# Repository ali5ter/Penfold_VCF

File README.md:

> **⚠️ Archived 2025-08-25. No longer maintained.**

# Penfold_VCF
[KiCad](https://www.kicad.org/) project for the circuit and PCB of R.A. Penfolds VCF design which I adapted as a Eurorack powered module.
The original circuit is taken from [the book, "Electronic Synthesiser Construction" by R. A. Penfold](https://sdiy.info/wiki/Penfold_synthesiser), published by Babani in 1986.

I have kept to the original design as much as possible, but added power and switched INT.CV via [a Eurorack spec bus](https://doepfer.de/home_e.htm).

The circuit and PCB are verfied to work and being used as part of my modular build.

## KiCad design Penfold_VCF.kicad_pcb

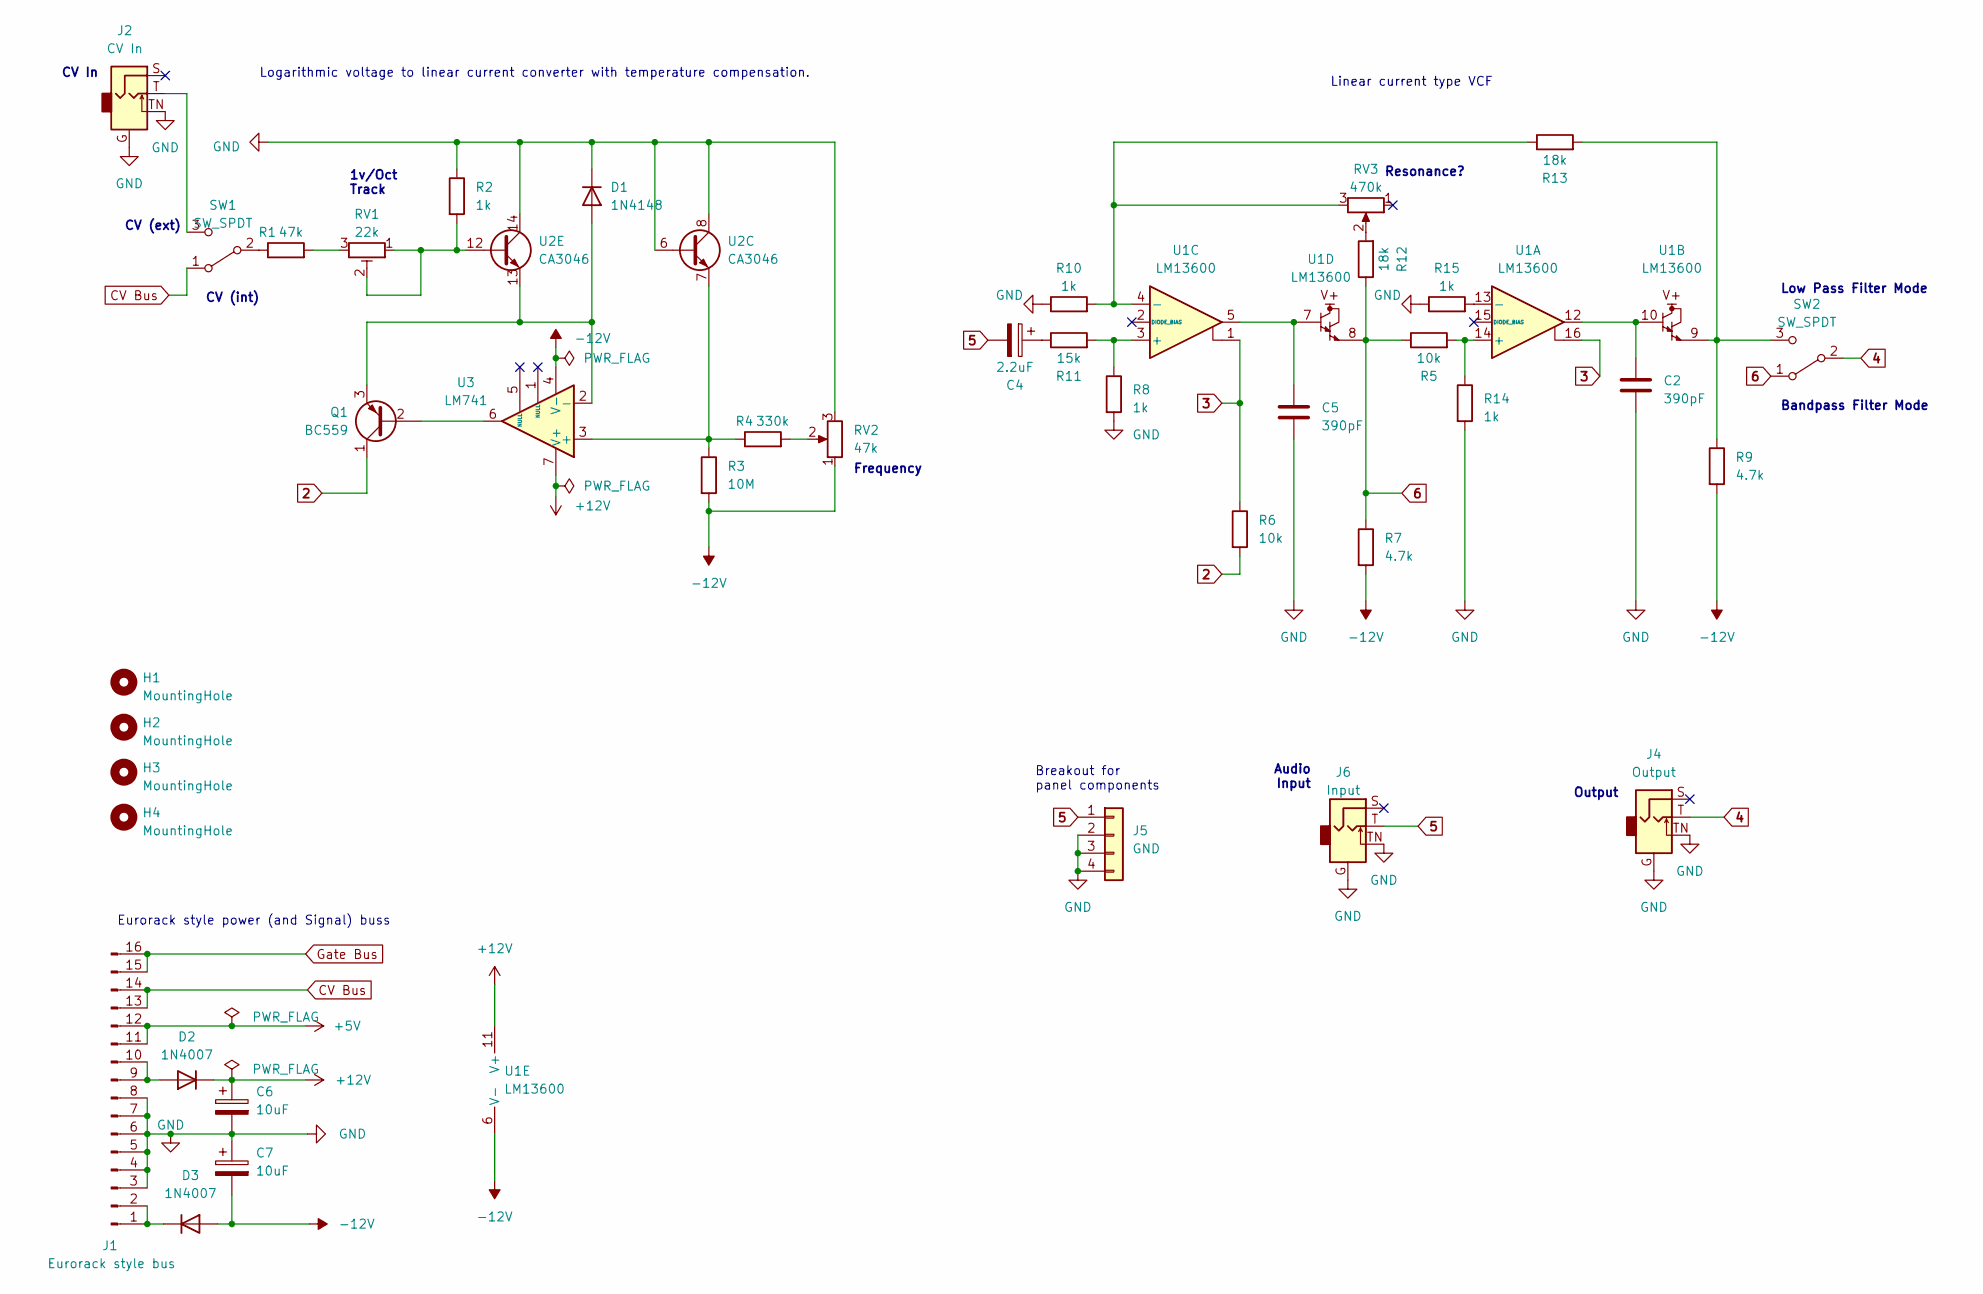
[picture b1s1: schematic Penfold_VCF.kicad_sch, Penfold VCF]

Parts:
C2, C5: 390pF; C_Disc_D5.0mm_W2.5mm_P5.00mm
C4: 2.2uF; CP_Radial_D5.0mm_P2.00mm
C6, C7: 10uF; CP_Radial_D5.0mm_P2.00mm
D1: 1N4148; D_DO-35_SOD27_P7.62mm_Horizontal
D2, D3: 1N4007; D_DO-41_SOD81_P10.16mm_Horizontal
H1, H2, H4: MountingHole; MountingHole_3.2mm_M3
H3: MountingHole; MountingHole_3mm
J1: Eurorack style bus; PinHeader_2x08_P2.54mm_Vertical
J2: CV In
J4: Output
J5: GND; PinHeader_1x04_P2.54mm_Vertical
J6: Input
Q1: BC559; TO-92_Inline
R1: 47k; R_Axial_DIN0207_L6.3mm_D2.5mm_P10.16mm_Horizontal
R2, R8, R10, R14, R15: 1k; R_Axial_DIN0207_L6.3mm_D2.5mm_P10.16mm_Horizontal
R3: 10M; R_Axial_DIN0207_L6.3mm_D2.5mm_P10.16mm_Horizontal
R4: 330k; R_Axial_DIN0207_L6.3mm_D2.5mm_P10.16mm_Horizontal
R5, R6: 10k; R_Axial_DIN0207_L6.3mm_D2.5mm_P10.16mm_Horizontal
R7, R9: 4.7k; R_Axial_DIN0207_L6.3mm_D2.5mm_P10.16mm_Horizontal
R11: 15k; R_Axial_DIN0207_L6.3mm_D2.5mm_P10.16mm_Horizontal
R12, R13: 18k; R_Axial_DIN0207_L6.3mm_D2.5mm_P10.16mm_Horizontal
RV1: 22k; PinHeader_1x03_P2.54mm_Vertical
RV2: 47k; PinHeader_1x03_P2.54mm_Vertical
RV3: 470k; PinHeader_1x03_P2.54mm_Vertical
SW1, SW2: SW_SPDT; PinHeader_1x03_P2.54mm_Vertical
U1: LM13600; DIP-16_W7.62mm_Socket_LongPads
U2: CA3046; DIP-14_W7.62mm_Socket
U3: LM741; DIP-8_W7.62mm_Socket_LongPads

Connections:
2: Q1.1 (C), R6.2
3: R6.1, U1.1, U1.16
4: J4.T, SW2.2 (B)
5: C4.2, J5.1, J6.T
6: R5.1, R7.1, R12.1, SW2.1 (A), U1.8
+5V: J1.11, J1.12
+12V: C6.1, D2.1 (K), U1.11 (V+), U3.7 (V+)
-12V: C7.2, D3.2 (A), R3.2, R7.2, R9.2, RV2.1, U1.6 (V-), U3.4 (V-)
CV Bus: J1.13, J1.14, SW1.1 (A)
GND: C2.2, C5.2, C6.2, C7.1, D1.1 (K), J1.3, J1.4, J1.5, J1.6, J1.7, J1.8, J2.G, J2.TN, J4.G, J4.TN, J5.2, J5.3, J5.4, J6.G, J6.TN, R2.1, R8.2, R10.1, R14.2, R15.1, RV2.3, U2.6 (B3), U2.8 (C3), U2.14 (C5)
Gate Bus: J1.15, J1.16
unnamed: C2.1, U1.10, U1.12
unnamed: C4.1, R11.1
unnamed: C5.1, U1.5, U1.7
unnamed: D1.2 (A), Q1.3 (E), U2.13 (E5), U3.2 (-)
unnamed: D2.2 (A), J1.9, J1.10
unnamed: D3.1 (K), J1.1, J1.2
unnamed: Q1.2 (B), U3.6
unnamed: R1.2, RV1.3
unnamed: R4.2, RV2.2
unnamed: R12.2, RV3.2
unnamed: R1.1, SW1.2 (B)
unnamed: J2.T, SW1.3 (C)
unnamed: R9.1, R13.2, SW2.3 (C), U1.9
unnamed: R5.2, R14.1, U1.14 (+)
unnamed: R15.2, U1.13 (-)
unnamed: R8.1, R11.2, U1.3 (+)
unnamed: R10.2, R13.1, RV3.3, U1.4 (-)
unnamed: R3.1, R4.1, U2.7 (E3), U3.3 (+)
unnamed: R2.2, RV1.1, RV1.2, U2.12 (B5)

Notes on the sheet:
CV In
Linear current type VCF
CV (ext)
Eurorack style power (and Signal) buss
CV (int)
Low Pass Filter Mode
Output
Frequency
Resonance?
Breakout for panel components
Logarithmic voltage to linear current converter with temperature compensation.
Audio Input
Bandpass Filter Mode
1v/Oct Track

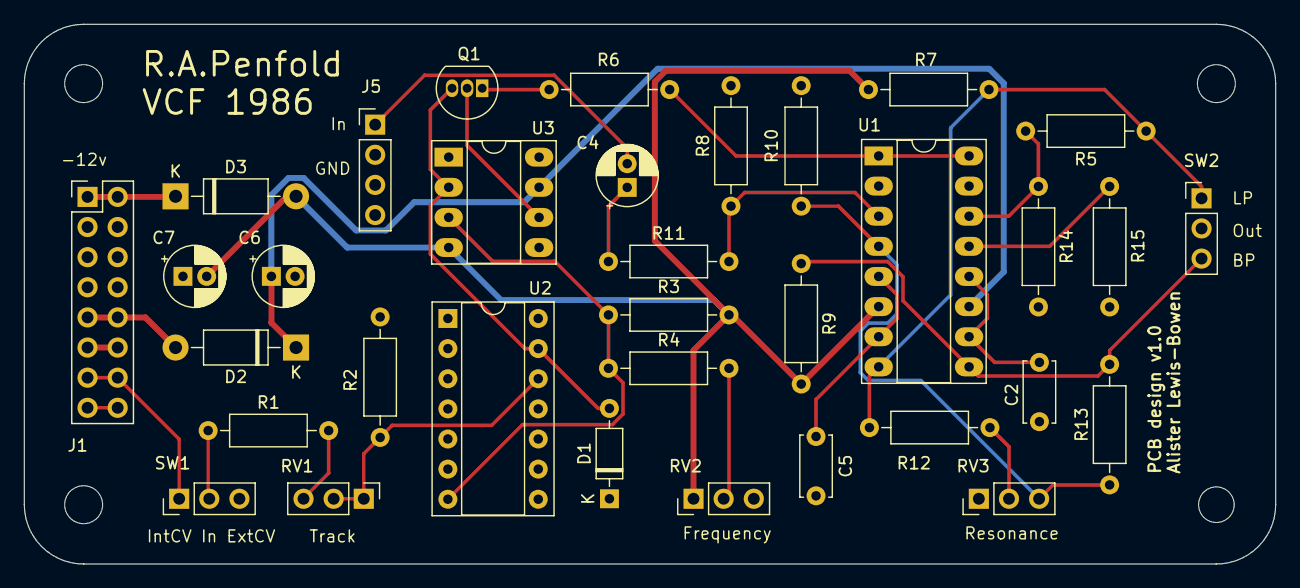
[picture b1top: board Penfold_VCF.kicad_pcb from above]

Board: 2 copper layers, 105.5 x 45.5 mm, 38 parts (0 on the bottom side), 28 nets.

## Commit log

2023-07-07 initial comment
2025-08-21 docs: sync archive banner
